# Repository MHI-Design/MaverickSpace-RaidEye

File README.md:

# Raid Eye - Kamikaze İHA Sinyal Tespit ve İkaz Sistemi

## Proje Tanıtımı
Raid Eye projesi, askerlerimizin güvenliğini tehdit eden kamikaze insansız hava araçlarına (İHA) karşı önlem almak için geliştirilmiştir. Projenin temel amacı şu şekilde özetlenebilir:

Kamikaze İHA'ların 5.8 GHz frekansındaki kontrol ve görüntü aktarım sinyallerini tespit etmek
Bu sinyallerin kuvvetini ölçerek yaklaşan tehlikeyi belirlemek
Tespit edilen tehlikeyi sesli uyarı sistemiyle askerlerimize bildirerek önlem alınmasını sağlamak
Böylece, FPV (First Person View) teknolojisi kullanan kamikaze İHA'ların neden olabileceği kayıpların önüne geçilmesi hedeflenmektedir. Maverick Space ekibi, askeri operasyonlarda
bilinmeyen alanlarda karşılaşılabilecek bu tehdidin önlenmesi için Raid Eye projesini geliştirmiştir.

Kısaca, Raid Eye sistemi, 5.8 GHz frekansındaki sinyalleri algılayarak yaklaşan kamikaze İHA'lara karşı askerlerimizi önceden uyaran bir güvenlik çözümüdür.

Donanım Tasarım Görselleri

https://github.com/MHI-Embedded-Dev/MaverickSpace-RaidEye/assets/132624287/f9e3f8c7-b252-42bd-ad0d-98eca6fa7957

Sistem blok şeması

Gömülü yazılımın çalıtığını proteus ile simüle edilmiştir.

## Dosya Yapısı
- **Donanım Tasarım/**: PCB tasarım dosyaları, montaj animasyon videosu ve 3D kutu tasarımı.
- **Gömülü Yazılımı/**: Gömülü yazılım kaynak kodları ve dokümantasyonu.
- **Mobil Uygulama Yazılımı/**: Arayüz yazılımı kaynak kodları ve dokümantasyonu.
- **Rapor ve Sunum/**: Proje raporları ve sunumları.

## Kurulum ve Çalıştırma
### Donanım
- PCB dosyalarını `Donanım Tasarımı\hecatlon_raid_eye\gerber_to_order` klasöründen indirin ve bir PCB üreticisine gönderin.
-Raid Eye kartının dizgisi için gerekli olan dosyaları ‘Donanım Tasarımı\hecatlon_raid_eye\bom’ malzemeler sipariş verilerek dizgi işlemi yapılabilir.
- Montaj talimatlarına `Donanım Tasarımı\hecatlon_raid_eye\bom` dosyasından ulaşabilirsiniz. Dizgi işleminde süreci hızlandırma bir eklenti ile hazırlanmıştır.

### Gömülü Yazılım
- Gömülü yazılım kaynak kodlarını iki kısıma ayrılmaktadır. ESP32 ve STM32 tarafı olmak üzere STM32 kodları `Gömülü Yazılımı\STM32F446RE\Hecaton_Raid_EYE\Core\Src\main.c` algoritma işleyişi ve sensörleri okuma işlemini yapar. klasöründen bulun.
-ESP32 kodları ‘Gömülü Yazılımı\ESP32-WROOM\Raid_Eye_ESP32’ bluetooth ile mobil uygulamaya bağlantısı gerçekleştirilir. Yapılan sinyal ölçümleri ve ikaz durumu mobil uygulamaya iletilmektedir.
- Yazılımın nasıl yükleneceği ve çalıştırılacağı ile ilgili bilgi için 
ESP32 kodu ve çalıştırma readme dosyası`C:\Github\MaverickSpace-RaidEye\Gömülü Yazılımı\ESP32-WROOM\Raid_Eye_ESP32\readme.txt` dosyasına bakın.
STM32  kodu ve çalıştırma readme dosyası` Gömülü Yazılımı\STM32F446RE\Hecaton_Raid_EYE` dosyasına bakın.

### Arayüz Yazılımı
- Arayüz yazılımı kaynak kodlarını ` Mobil Uygulama Yazılımı\uygulama\src\main.c` klasöründen bulun.
- Mobil Uygulama kodu ve çalıştırma readme dosyası ‘Mobil Uygulama Yazılımı\uygulama\README.txt’ dosyasına bakın.

## İletişim
Muhammed Hüseyin İSMAİL -> mhi.hsynn@gmail.com

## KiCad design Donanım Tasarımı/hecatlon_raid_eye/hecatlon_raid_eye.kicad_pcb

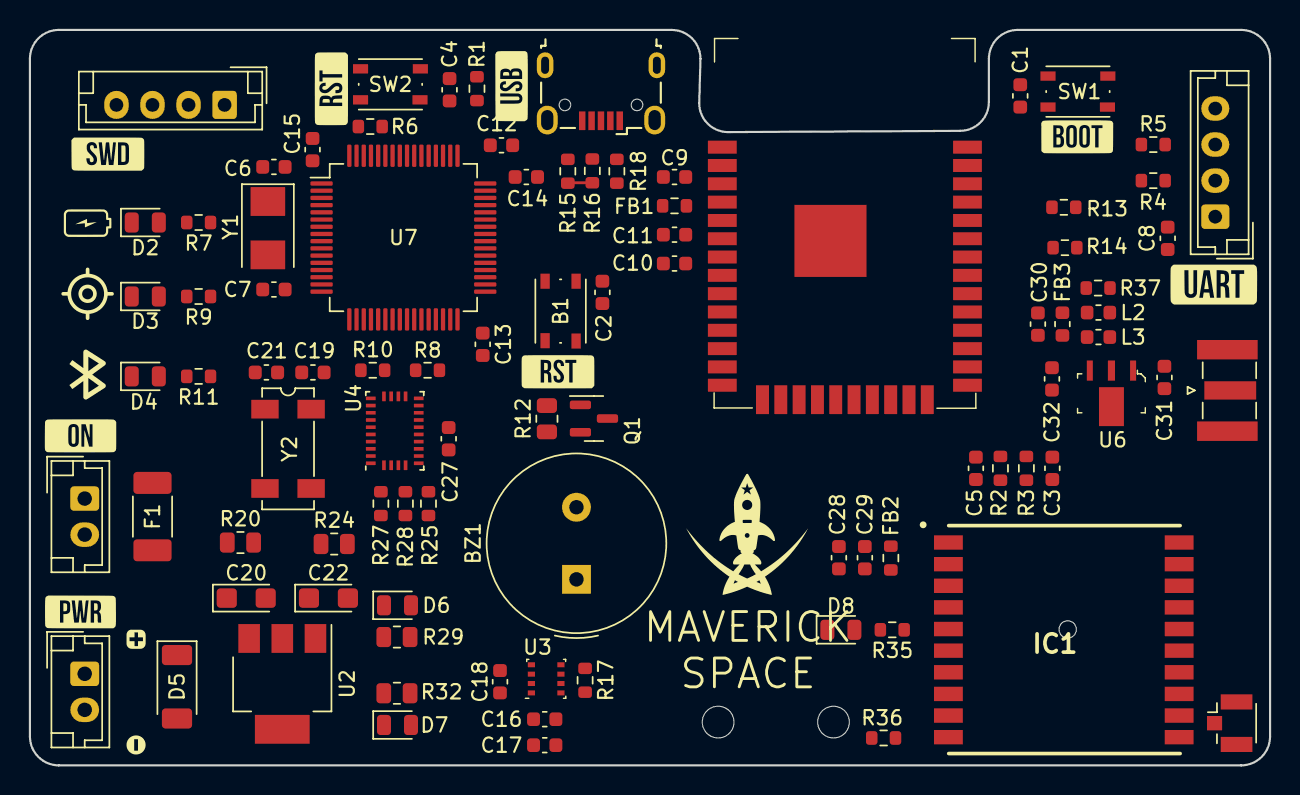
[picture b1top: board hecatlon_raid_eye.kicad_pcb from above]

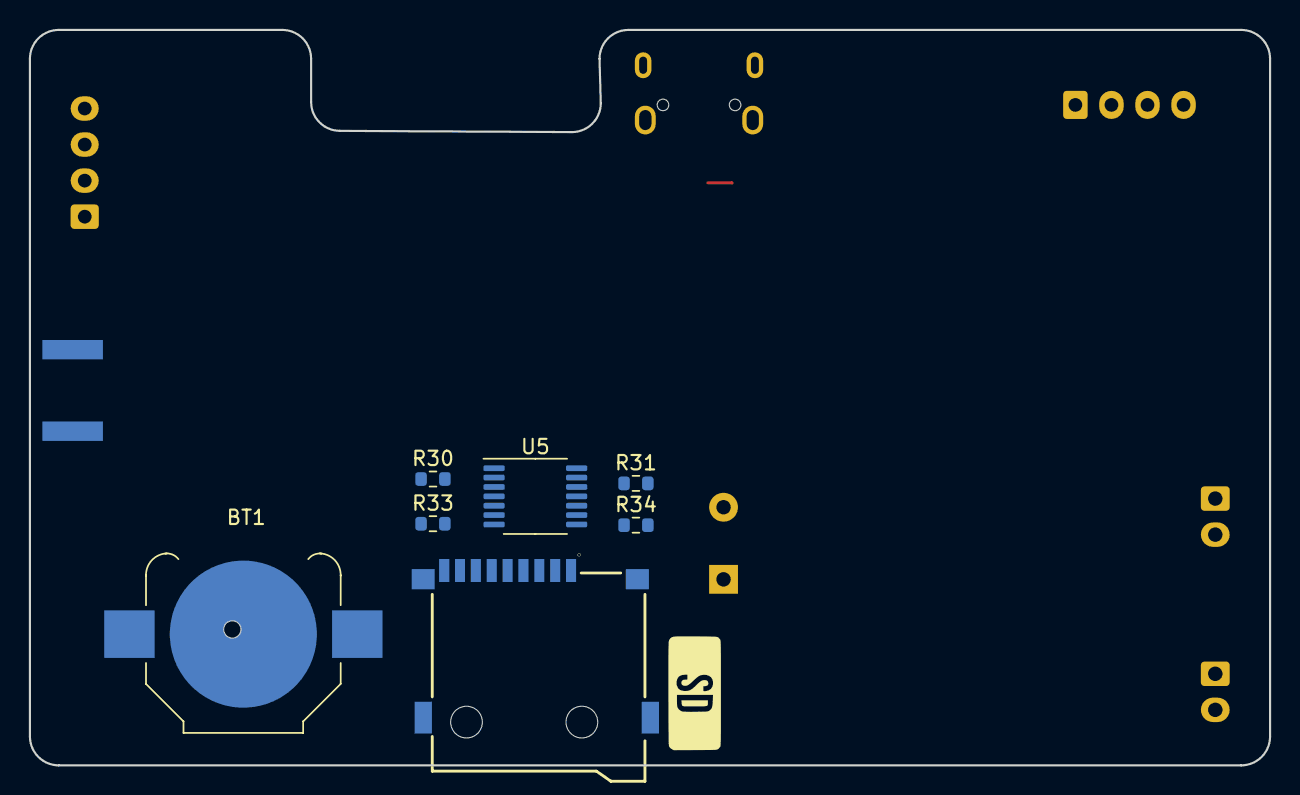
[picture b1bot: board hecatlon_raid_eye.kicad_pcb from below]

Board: 4 copper layers, 86.0 x 51.0 mm, 97 parts (7 on the bottom side), 76 nets.

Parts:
AE1: Antenna_Shield; U.FL_Hirose_U.FL-R-SMT-1_Vertical
AE2: Antenna_Shield; SMA_Samtec_SMA-J-P-X-ST-EM1_EdgeMount
B1: RESET; SW_Push_1P1T_NO_Vertical_Wuerth_434133025816
BT1: CR1220; BatteryHolder_Keystone_3000_1x12mm
BZ1: Buzzer; Buzzer_TDK_PS1240P02BT_D12.2mm_H6.5mm
C1, C3, C4, C9, C11: 100nF; C_0603_1608Metric
C2, C12, C13, C14, C15, C16, C18, C27, C29: 100n; C_0603_1608Metric
C5: 1nF; C_0603_1608Metric
C6, C7: 10p; C_0603_1608Metric
C8, C10: 10uF; C_0603_1608Metric
C17, C28: 2.2uF; C_0603_1608Metric
C19, C21: 22p; C_0603_1608Metric
C20, C22: 10uF; CP_EIA-3216-18_Kemet-A
C30, C31, C32: 47nF; C_0603_1608Metric
D2, D7, D8: RED; LED_0805_2012Metric
D3: BLUE; LED_0805_2012Metric
D4, D6: GREEN; LED_0805_2012Metric
D5: 1N4007; D_SOD-128
F1: 1A; Fuse_2010_5025Metric_Pad1.52x2.65mm_HandSolder
FB1, FB2: 100R; R_0603_1608Metric
FB3: 1600R; L_0603_1608Metric
IC1: FGPMMOPA6H
J1, J2: SWD; JST_EH_B4B-EH-A_1x04_P2.50mm_Vertical
J3: Anahtar; JST_EH_B2B-EH-A_1x02_P2.50mm_Vertical
J5: USB_B_Mini; USB_Micro-B_Wuerth_629105150521
J6: Power; JST_EH_B2B-EH-A_1x02_P2.50mm_Vertical
J10: Micro_SD_Card; L-KLS1-TF-003-H1.85-R
L2: 110nH; L_0603_1608Metric
L3: 33nH; L_0603_1608Metric
MOD1: ESP32-WROOM-32; ESP32-WROOM-32D
Q1: BC817; SOT-23
R1, R6, R8, R10, R17, R25, R27, R28: 10k; R_0603_1608Metric
R2: 26R; R_0603_1608Metric
R3: 0.8R; R_0603_1608Metric
R4, R5: 0R; R_0603_1608Metric
R7, R9, R11, R35: 470R; R_0603_1608Metric
R12: 470R; R_0805_2012Metric
R13, R14: 2.2k; R_0603_1608Metric
R15: 1.5k; R_0603_1608Metric
R16, R18: 1R; R_0603_1608Metric
R20: 680k; R_0805_2012Metric
R24: 100k; R_0805_2012Metric
R29: 1K; R_0805_2012Metric
R30, R31, R33, R34: 3.3K; R_0603_1608Metric
R32: 10K; R_0805_2012Metric
R36: 10K; R_0603_1608Metric
R37: OPS; R_0603_1608Metric
SW1: BOOT; SW_Push_1P1T_NO_Vertical_Wuerth_434133025816
SW2: RESET; SW_Push_1P1T_NO_Vertical_Wuerth_434133025816
U2: AMS1117-3.3; SOT-223-3_TabPin2
U3: BME280; Bosch_LGA-8_2.5x2.5mm_P0.65mm_ClockwisePinNumbering
U4: BNO055; LGA-28_5.2x3.8mm_P0.5mm
U5: 74LVC125A; TSSOP-14_4.4x5mm_P0.65mm
U6: SKY65017-70LF; TO-243AA
U7: STM32F446RETx; LQFP-64_10x10mm_P0.5mm
Y1: 8MHz; Crystal_SMD_5032-2Pin_5.0x3.2mm
Y2: 32.768Khz; Crystal_SMD_SeikoEpson_MC306-4Pin_8.0x3.2mm

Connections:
+3.3V: C8.2, C10.2, C11.1, C12.1, C13.1, C14.1, C15.1, C16.2, C17.1, C18.1, C22.1, C28.1, C29.1, C30.2, FB1.1, FB2.2, FB3.1, J1.1, J2.1, J10.4 (VDD), R1.1, R8.1, R10.1, R13.1, R14.1, R15.1, R29.1, R36.2, U2.2 (VO), U3.2 (CSB), U3.6 (VDDIO), U3.8 (VDD), U4.3 (VDD), U4.4 (~BOOT_LOAD_PIN), U4.28 (VDDIO), U5.14 (VCC), U7.1 (VBAT), U7.13 (VDDA), U7.19 (VDD), U7.32 (VDD), U7.48 (VDD), U7.64 (VDD)
/CS_LLS: J10.2 (DAT3/CD), U5.8 (3Y)
/DI_LLS: J10.3 (CMD), U5.3 (1Y)
/DO_LLS: J10.7 (DAT0), R31.2
/EN: C4.1, MOD1.3 (EN), R1.2, SW2.2
/GPS_FIX: IC1.5 (3D-FIX), R35.1
/IO_0: C1.1, MOD1.25 (IO0), SW1.2
/SCK_LLS: J10.5 (CLK), U5.6 (2Y)
/UART_RXD0: J1.2, R4.2
/UART_TXD0: J1.3, R5.2
BAT_LEVEL: MOD1.14 (IO12), R20.2, R24.1
BNO_INT: U4.14 (INT), U7.57 (PB5)
BNO_RST: U4.11 (~RESET), U7.56 (PB4)
BOOT0: R6.2, U7.60 (BOOT0)
BUZZER: MOD1.7 (IO35), R12.1
CS: MOD1.29 (IO5), R34.2
GND: AE1.2 (Shield), AE2.2 (Shield), B1.2 (K), BT1.2 (-), C1.2, C2.2, C4.2, C5.1, C6.2, C7.2, C8.1, C9.2, C10.1, C11.2, C12.2, C13.2, C14.2, C15.2, C16.1, C17.2, C18.2, C19.2, C20.2, C21.2, C22.2, C27.2, C28.2, C29.2, C30.1, D2.1 (K), D3.1 (K), D4.1 (K), D6.1 (K), D7.1 (K), D8.1 (K), IC1.3 (GND_1), IC1.8 (GND_2), IC1.12 (GND_3), IC1.19 (GND_4), J1.4, J2.4, J5.4 (ID), J5.5 (GND), J5.6 (Shield), J6.2, J10.6 (VSS), J10.9 (SHIELD), MOD1.1 (GND), MOD1.15 (GND), MOD1.38 (GND), MOD1.39 (GND), Q1.2 (E), R3.1, R6.1, R17.2, R24.2, R25.1, R27.1, R28.2, SW1.1, SW2.1, U2.1 (GND), U3.1 (GND), U3.7 (GND), U4.2 (GND), U4.10 (BL_IND), U4.15 (GNDIO), U4.16 (GNDIO), U4.18 (COM2), U4.25 (GNDIO), U5.1 (1OE), U5.4 (2OE), U5.7 (GND), U5.10 (3OE), U5.13 (4OE), U6.2 (GND), U6.4 (GND), U7.12 (VSSA), U7.18 (VSS), U7.31 (VSS), U7.47 (VSS), U7.63 (VSS), Y2.2, Y2.3
GPS_PPS: IC1.13 (1PPS), U7.41 (PA8)
GPS_RX: IC1.9 (TX), U7.43 (PA10)
GPS_TX: IC1.10 (RX), R36.1, U7.42 (PA9)
GPS_VBACKUP: BT1.1 (+), IC1.4 (VBACKUP)
I2C1_SCL: MOD1.36 (IO22), R13.2, U7.58 (PB6)
I2C1_SDA: MOD1.33 (IO21), R14.2, U7.59 (PB7)
I2C2_SCL: R8.2, U3.4 (SCK), U4.19 (COM1), U7.29 (PB10)
I2C2_SDA: R10.2, U3.3 (SDI), U4.20 (COM0), U7.53 (PC12)
LED1: R7.1, U7.14 (PA0)
LED2: R9.1, U7.15 (PA1)
LED3: R11.1, U7.16 (PA2)
MISO: MOD1.31 (IO19), U5.11 (4Y)
MOSI: MOD1.37 (IO23), R30.1
NRST: B1.1 (2), C2.1, U7.7 (NRST)
unnamed: AE1.1 (A), IC1.11 (EX_ANT)
unnamed: AE2.1 (A), C31.1
unnamed: BZ1.2 (+), Q1.3 (C)
unnamed: C3.2, R2.1, R3.2
unnamed: D2.2 (A), R7.2
unnamed: D3.2 (A), R9.2
unnamed: D4.2 (A), R11.2
unnamed: D5.2 (A), J6.1
unnamed: D5.1 (K), J3.2
unnamed: D6.2 (A), R29.2
unnamed: D7.2 (A), R32.2
unnamed: D8.2 (A), R35.2
unnamed: FB3.2, L2.1, R37.1
unnamed: FB2.1, IC1.1 (VCC)
unnamed: F1.2, J3.1
unnamed: J5.3 (D+), R16.1
unnamed: J5.2 (D-), R18.1
unnamed: L2.2, L3.1, R37.2
unnamed: C9.1, FB1.2, MOD1.2 (3V3)
unnamed: MOD1.34 (RXD0), R5.1
unnamed: MOD1.35 (TXD0), R4.1
unnamed: Q1.1 (B), R12.2
unnamed: R17.1, U3.5 (SDO)
unnamed: C27.1, U4.9 (CAP)
unnamed: R28.1, U4.17 (COM3)
unnamed: R25.2, U4.6 (PS0)
unnamed: R27.2, U4.5 (PS1)
unnamed: C21.1, U4.27 (XIN32), Y2.1
unnamed: C19.1, U4.26 (XOUT32), Y2.4
unnamed: R30.2, U5.2 (1A)
unnamed: R33.2, U5.5 (2A)
unnamed: R34.1, U5.9 (3A)
unnamed: R31.1, U5.12 (4A)
unnamed: C31.2, U6.1 (IN)
unnamed: C32.1, L3.2, U6.3 (OUT)
OSC_IN: C6.1, U7.5 (PH0), Y1.1
OSC_OUT: C7.1, U7.6 (PH1), Y1.2
SCK: MOD1.30 (IO18), R33.1
SGN_FILTER: C5.2, MOD1.24 (IO2), R2.2
SGN_OUT: C3.1, C32.2
SW_CLK: J2.2, U7.49 (PA14)
SW_DIO: J2.3, U7.46 (PA13)
USB+: R15.2, R16.2, U7.45 (PA12)
USB-: R18.2, U7.44 (PA11)
VDD: BZ1.1 (-), C20.1, F1.1, R20.1, R32.1, U2.3 (VI)

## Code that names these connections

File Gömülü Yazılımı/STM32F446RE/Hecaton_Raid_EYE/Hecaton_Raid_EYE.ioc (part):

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Mcu.Name=STM32F446R(C-E)Tx
Mcu.Package=LQFP64
Mcu.UserName=STM32F446RETx
PA0-WKUP.GPIOParameters=GPIO_Label
PA0-WKUP.GPIO_Label=LED1
PA0-WKUP.Signal=GPIO_Output
PA1.GPIOParameters=GPIO_Label
PA1.GPIO_Label=LED2
PA1.Signal=GPIO_Output
PA10.GPIOParameters=GPIO_Label
PA10.GPIO_Label=GPS_RX1
PA10.Mode=Asynchronous
PA10.Signal=USART1_RX
PA11.Mode=Host_Only
PA11.Signal=USB_OTG_FS_DM
PA12.Mode=Host_Only
PA12.Signal=USB_OTG_FS_DP
PA13.Mode=Serial_Wire
PA13.Signal=SYS_JTMS-SWDIO
PA14.Mode=Serial_Wire
PA14.Signal=SYS_JTCK-SWCLK
PA2.GPIOParameters=GPIO_Label
PA2.GPIO_Label=LED3
PA2.Signal=GPIO_Output
PA8.GPIOParameters=GPIO_Label
PA8.GPIO_Label=GPS_PSS
PA8.Signal=S_TIM1_CH1
PA9.GPIOParameters=GPIO_Label
PA9.GPIO_Label=GPS_TX1
PA9.Mode=Asynchronous
PA9.Signal=USART1_TX
PB10.Mode=I2C
PB10.Signal=I2C2_SCL
PB4.GPIOParameters=GPIO_Label
PB4.GPIO_Label=BNO_RST
PB4.Signal=GPIO_Output
PB5.GPIOParameters=GPIO_Label
PB5.GPIO_Label=BNO_INT
PB5.Signal=GPIO_Output
PB6.Mode=I2C
PB6.Signal=I2C1_SCL
PB7.Mode=I2C
PB7.Signal=I2C1_SDA
PC0.GPIOParameters=GPIO_Label
PC0.GPIO_Label=BUZZER
PC0.Signal=GPIO_Output
PC10.Mode=Asynchronous
PC10.Signal=USART3_TX
PC12.Mode=I2C
PC12.Signal=I2C2_SDA
PC5.Mode=Asynchronous
PC5.Signal=USART3_RX
PH0-OSC_IN.Mode=HSE-External-Oscillator
PH0-OSC_IN.Signal=RCC_OSC_IN
PH1-OSC_OUT.Mode=HSE-External-Oscillator
PH1-OSC_OUT.Signal=RCC_OSC_OUT
RCC.HSE_VALUE=25000000
RCC.SYSCLKFreq_VALUE=120000000
RCC.SYSCLKSource=RCC_SYSCLKSOURCE_PLLCLK
board=custom

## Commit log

2024-05-31 İndir Başlat
    Kamikaze İHA Sinyal Tespit ve İkaz Sistemi
    ✓ Donanım Tasarımı
    ✓ Gömülü Yazılımı
    ✓ Arayüz Tasarımı
    ✓ Raporlama
    ✓ Sunum
2024-05-31 Create README.md
    Maverick Space'in Ride Eye uygulaması kılavuzu...
